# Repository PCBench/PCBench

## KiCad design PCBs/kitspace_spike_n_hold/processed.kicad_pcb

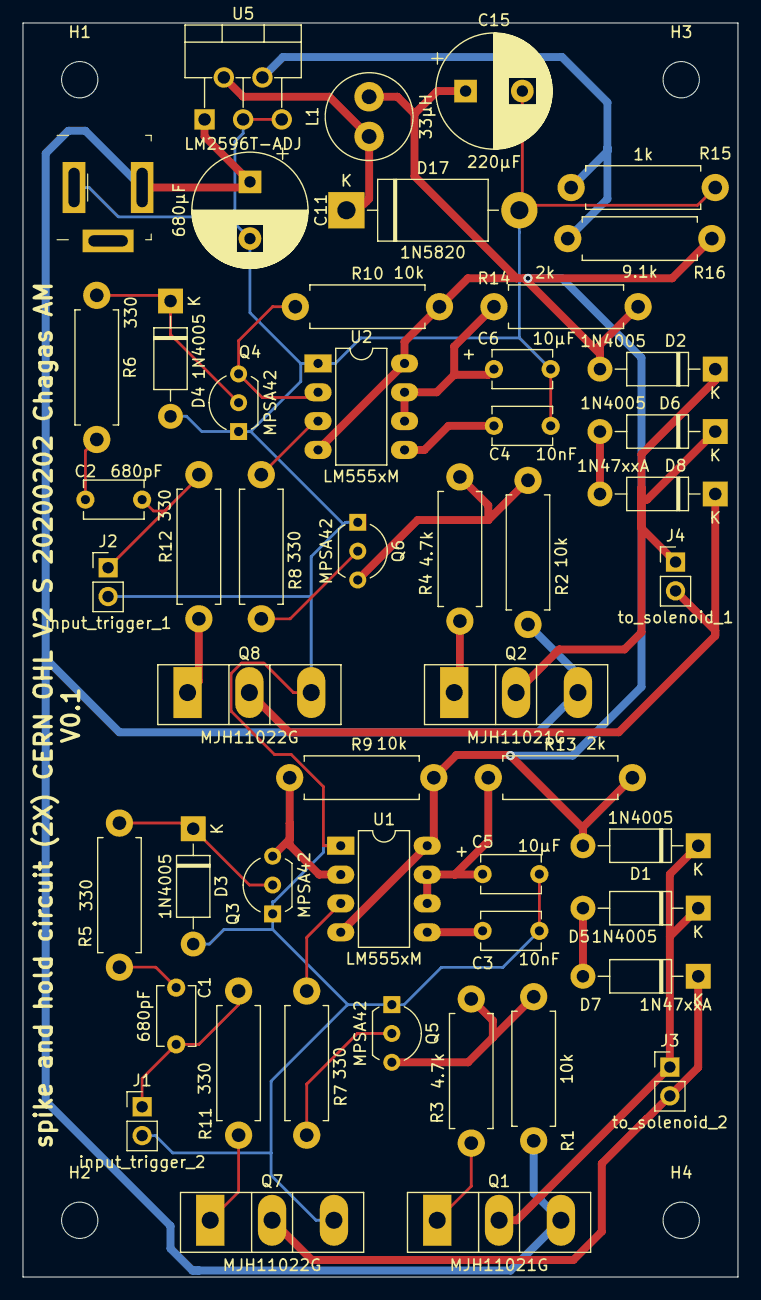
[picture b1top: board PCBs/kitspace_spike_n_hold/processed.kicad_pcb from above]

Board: 2 copper layers, 63.0 x 110.5 mm, 54 parts (0 on the bottom side), 33 nets.

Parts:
C1, C2: 680pF; C_Disc_D5.1mm_W3.2mm_P5.00mm
C3, C4: 10nF; C_Disc_D5.1mm_W3.2mm_P5.00mm
C5, C6: 10µF; C_Disc_D5.1mm_W3.2mm_P5.00mm
C11: 680µF; CP_Radial_D10.0mm_P5.00mm
C15: 220µF; CP_Radial_D10.0mm_P5.00mm
D1, D2, D3, D4, D5, D6: 1N4005; D_DO-41_SOD81_P10.16mm_Horizontal
D7, D8: 1N47xxA; D_DO-41_SOD81_P10.16mm_Horizontal
D17: 1N5820; D_DO-201AD_P15.24mm_Horizontal
H1, H2, H3, H4: MountingHole; MountingHole_3.2mm_M3
J1: input_trigger_2; PinHeader_1x02_P2.54mm_Vertical
J2: input_trigger_1; PinHeader_1x02_P2.54mm_Vertical
J3: to_solenoid_2; PinHeader_1x02_P2.54mm_Vertical
J4: to_solenoid_1; PinHeader_1x02_P2.54mm_Vertical
J9: Barrel_Jack_MountingPin; Barrel_Jack_5.5mmODx2.1mmID_PJ-202A
L1: 33µH; L_Radial_D7.5mm_P3.50mm_Fastron_07P
Q1, Q2: MJH11021G; TO-247-3_Vertical
Q3, Q4, Q5, Q6: MPSA42; TO-92L_Inline_Wide
Q7, Q8: MJH11022G; TO-247-3_Vertical
R1, R2, R9, R10: 10k; R_Axial_DIN0411_L9.9mm_D3.6mm_P12.70mm_Horizontal
R3, R4: 4.7k; R_Axial_DIN0411_L9.9mm_D3.6mm_P12.70mm_Horizontal
R5, R6, R7, R8, R11, R12: 330; R_Axial_DIN0411_L9.9mm_D3.6mm_P12.70mm_Horizontal
R13, R14: 2k; R_Axial_DIN0411_L9.9mm_D3.6mm_P12.70mm_Horizontal
R15: 1k; R_Axial_DIN0411_L9.9mm_D3.6mm_P12.70mm_Horizontal
R16: 9.1k; R_Axial_DIN0411_L9.9mm_D3.6mm_P12.70mm_Horizontal
U1, U2: LM555xM; DIP-8_W7.62mm_LongPads
U5: LM2596T-ADJ; TO-220-5_P3.4x3.7mm_StaggerOdd_Lead3.8mm_Vertical

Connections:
+12V: C15.1, D1.2, D2.2, L1.2, R9.2, R10.2, R13.2, R14.2, R16.2, U1.4, U1.8, U2.4, U2.8
+24V: C11.1, J9.1, Q1.3, Q2.3, R1.1, R2.1, U5.1
GND: C3.1, C4.1, C5.2, C6.2, C11.2, C15.2, D3.2, D4.2, D17.2, J1.2, J2.2, J9.2, Q3.1, Q4.1, Q5.1, Q6.1, Q7.3, Q8.3, R15.1, U1.1, U2.1, U5.3, U5.5
unnamed: C1.1, R5.2
unnamed: C2.1, R6.2
unnamed: C3.2, U1.5
unnamed: C4.2, U2.5
unnamed: C5.1, R13.1, U1.6, U1.7
unnamed: C6.1, R14.1, U2.6, U2.7
unnamed: D1.1, D5.1, J3.1, Q1.2
unnamed: D2.1, D6.1, J4.1, Q2.2
unnamed: D3.1, Q3.2, R5.1
unnamed: D4.1, Q4.2, R6.1
unnamed: D5.2, D7.2
unnamed: D6.2, D8.2
unnamed: D7.1, J3.2, Q7.2
unnamed: D8.1, J4.2, Q8.2
unnamed: D17.1, L1.1, U5.2
unnamed: Q1.1, R3.2
unnamed: Q2.1, R4.2
unnamed: Q3.3, R9.1, U1.2
unnamed: Q4.3, R10.1, U2.2
unnamed: Q5.2, R7.1
unnamed: Q5.3, R1.2, R3.1
unnamed: Q6.2, R8.1
unnamed: Q6.3, R2.2, R4.1
unnamed: Q7.1, R11.1
unnamed: Q8.1, R12.1
unnamed: R15.2, R16.1, U5.4
input_trigger1: C2.2, J2.1, R12.2
input_trigger2: C1.2, J1.1, R11.2
timed_trigger1: R8.2, U2.3
timed_trigger2: R7.2, U1.3

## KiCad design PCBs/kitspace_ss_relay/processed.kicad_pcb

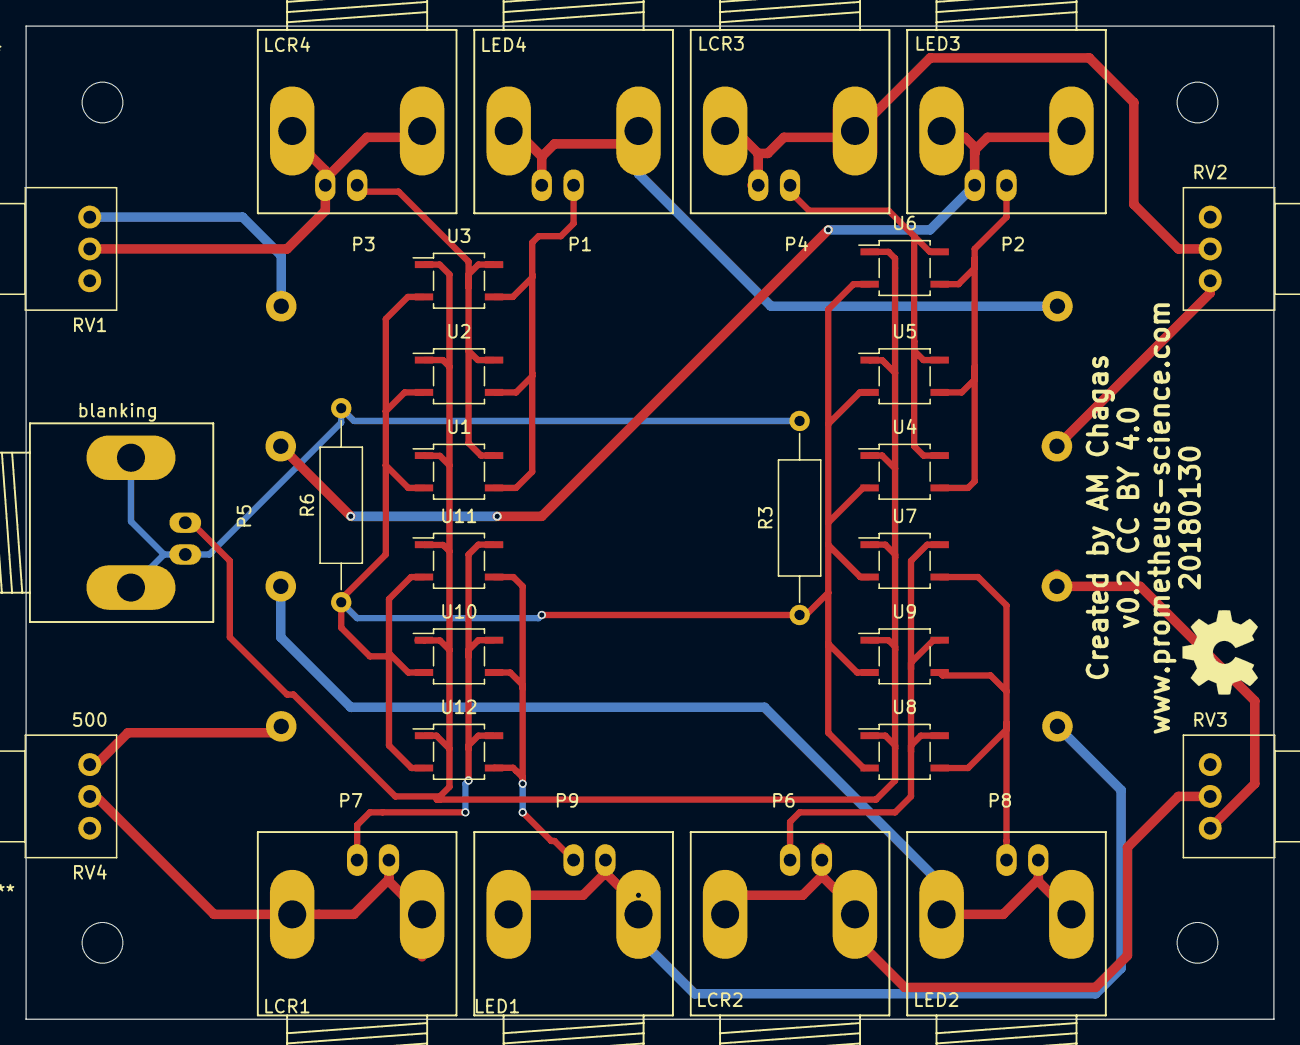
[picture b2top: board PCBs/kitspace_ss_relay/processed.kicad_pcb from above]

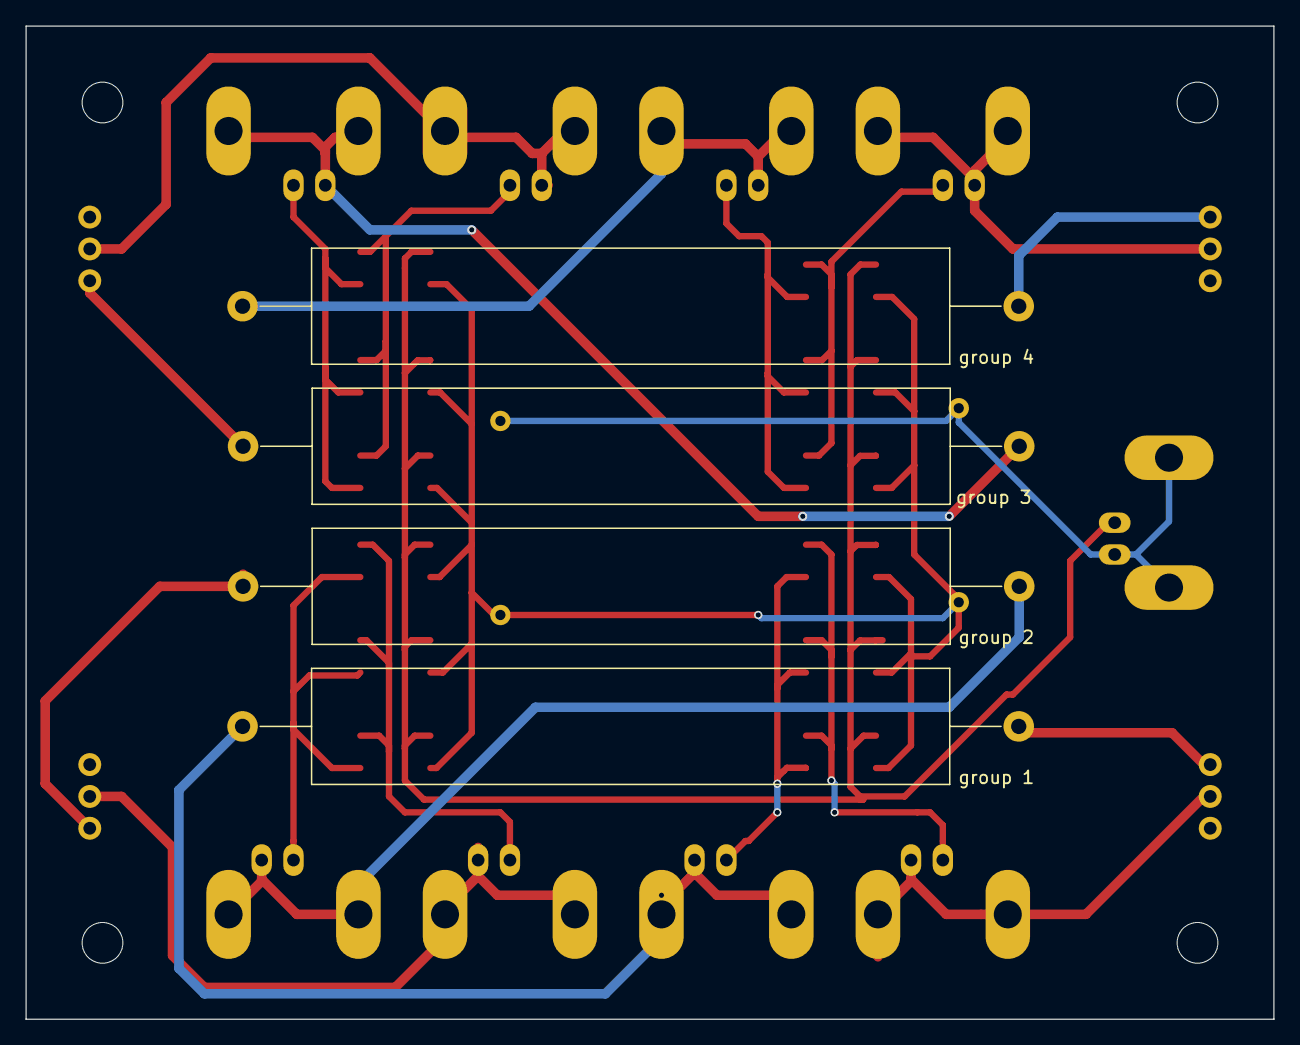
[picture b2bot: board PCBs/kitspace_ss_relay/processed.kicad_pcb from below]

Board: 2 copper layers, 98.0 x 78.0 mm, 31 parts (4 on the bottom side), 23 nets.

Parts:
P1: LED4; BNC_Socket_TYCO-AMP_LargePads
P2: LED3; BNC_Socket_TYCO-AMP_LargePads
P3: LCR4; BNC_Socket_TYCO-AMP_LargePads
P4: LCR3; BNC_Socket_TYCO-AMP_LargePads
P5: blanking; BNC_Socket_TYCO-AMP_LargePads
P6: LCR2; BNC_Socket_TYCO-AMP_LargePads
P7: LCR1; BNC_Socket_TYCO-AMP_LargePads
P8: LED2; BNC_Socket_TYCO-AMP_LargePads
P9: LED1; BNC_Socket_TYCO-AMP_LargePads
R3, R6: 270; R_Axial_DIN0309_L9.0mm_D3.2mm_P15.24mm_Horizontal
RV1, RV2, RV3, RV4: 500; Potentiometer_Alps_RK097_Single_Vertical
U1, U2, U3, U4, U5, U6, U7, U8, U9, U10, U11, U12: TLP291; SOP-4_3.8x4.1mm_Pitch2.54mm
group 1, group 2, group 3, group 4: 10; R_Axial_Power_L50.0mm_W9.0mm_P60.96mm

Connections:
GND: P5.2, R3.2, R6.2
unnamed: P1.1, U1.3, U2.3, U3.3
unnamed: P1.2, group 4.1
unnamed: P2.1, U4.3, U5.3, U6.3
unnamed: P2.2, group 3.1
unnamed: P3.1, U1.4, U2.4, U3.4
unnamed: P3.2, RV1.2
unnamed: P4.1, U4.4, U5.4, U6.4
unnamed: P4.2, RV2.2
unnamed: P5.1, U1.1, U2.1, U3.1, U4.1, U5.1, U6.1, U7.1, U8.1, U9.1, U10.1, U11.1, U12.1
unnamed: P6.1, U7.4, U8.4, U9.4
unnamed: P6.2, RV3.2
unnamed: P7.1, U10.4, U11.4, U12.4
unnamed: P7.2, RV4.2
unnamed: P8.1, U7.3, U8.3, U9.3
unnamed: P8.2, group 2.1
unnamed: P9.1, U10.3, U11.3, U12.3
unnamed: P9.2, group 1.1
unnamed: RV1.1, group 4.2
unnamed: RV2.1, group 3.2
unnamed: R3.1, R6.1, U1.2, U2.2, U3.2, U4.2, U5.2, U6.2, U7.2, U8.2, U9.2, U10.2, U11.2, U12.2
unnamed: RV3.1, group 2.2
unnamed: RV4.1, group 1.2

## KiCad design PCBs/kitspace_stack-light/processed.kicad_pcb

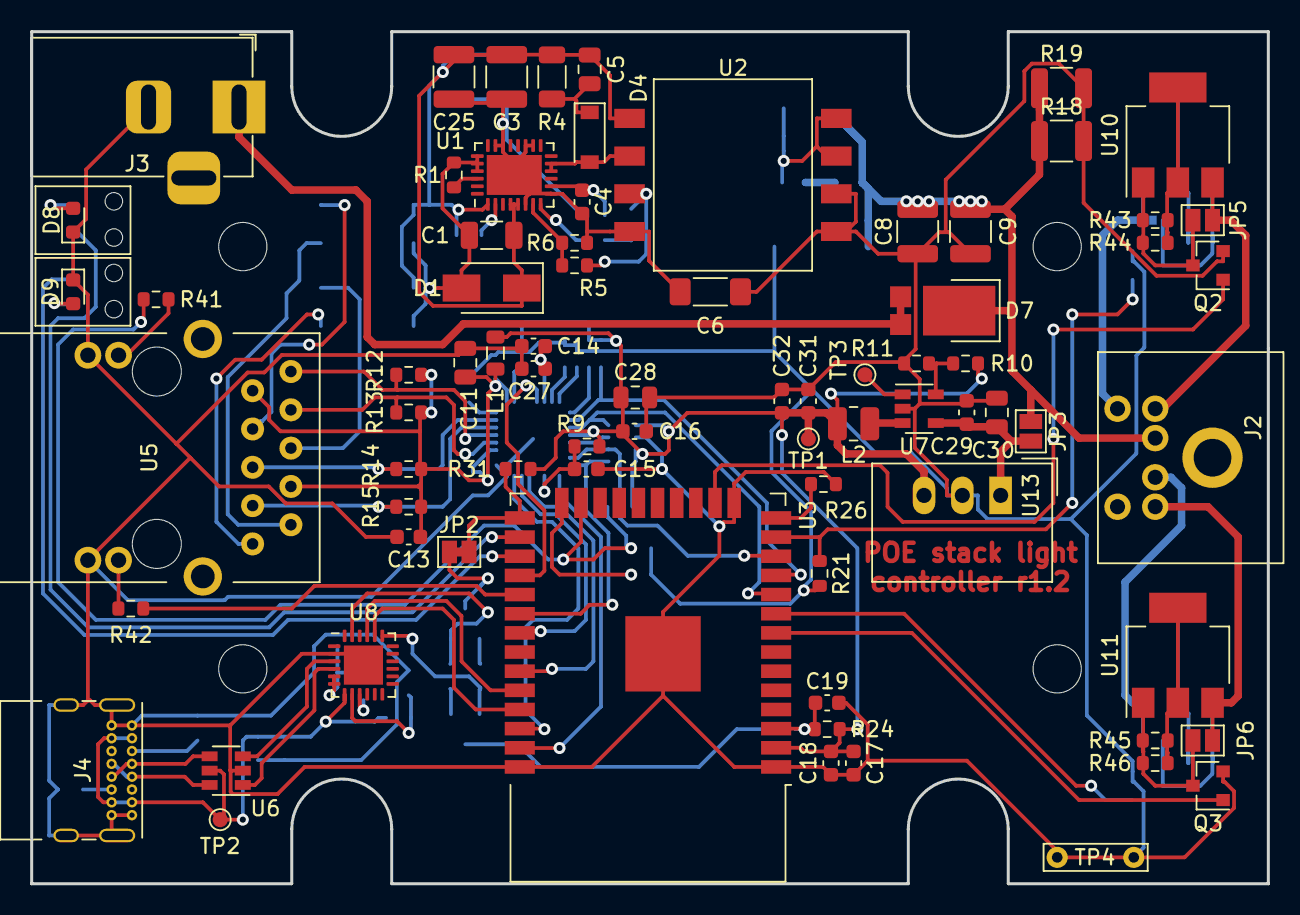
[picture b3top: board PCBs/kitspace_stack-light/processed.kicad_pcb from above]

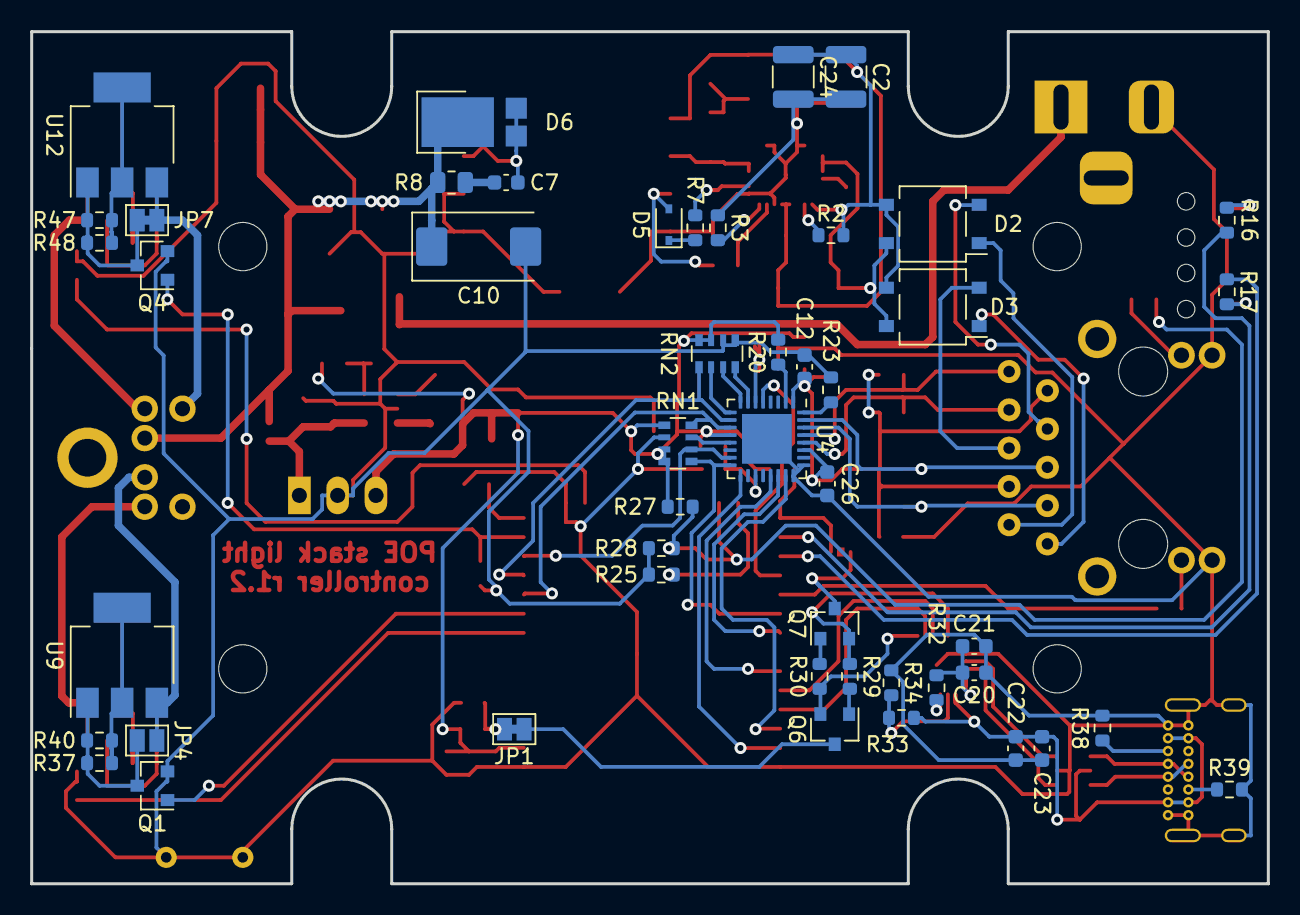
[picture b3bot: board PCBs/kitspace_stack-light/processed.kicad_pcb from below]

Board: 2 copper layers, 82.0 x 56.5 mm, 129 parts (48 on the bottom side), 94 nets.

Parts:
C1: 100n; C_1206_3216Metric
C2, C3, C24, C25: 2u2; C_1210_3225Metric
C4: 1U; C_0603_1608Metric
C5: 10n; C_0805_2012Metric
C6: 1000p; C_1806_4516Metric
C7: 1n; C_0603_1608Metric
C8, C9: 22u; C_1210_3225Metric
C10: 220u; CP_EIA-7343-31_Kemet-D
C11, C28: 22u; C_0805_2012Metric
C12, C14, C16, C18, C21, C23, C26, C29: 100n; C_0603_1608Metric
C13: 100nf; C_0603_1608Metric
C15, C19: 1u; C_0603_1608Metric
C17, C31, C32: 10u; C_0603_1608Metric
C20, C22: 4u7; C_0603_1608Metric
C27: 2u2; C_0603_1608Metric
C30: 10u; C_0805_2012Metric
D1: SMAJ58A; D_SMA
D2, D3: MB4S; TO-269AA
D4: BAV21; D_SOD-123
D5: 1N4148; D_SOD-323
D6, D7: SBR8U60P5; D_PowerDI-5
D8, D9: LED; LED_0603_1608Metric
H1, H2, H3, H4: MountingHole; MountingHole_3.2mm_M3
H5, H6: MountingHole; SLP3-150-150-R
J2: Mini-DIN-6; MD60S
J3: Barrel_Jack_Switch; BarrelJack_Horizontal
J4: USB_C_Receptacle_USB2.0; USB_C_Receptacle_GCT_USB4085
JP1, JP2, JP7: Jumper; SolderJumper-2_P1.3mm_Bridged_Pad1.0x1.5mm
JP3, JP4, JP5, JP6: Jumper; SolderJumper-2_P1.3mm_Open_Pad1.0x1.5mm
L1: FB; L_0805_2012Metric
L2: 10u; L_1008_2520Metric
Q1, Q2, Q3, Q4: 2N7002; SOT-23
Q6, Q7: BC817-40; SOT-23
R1: 62; R_0603_1608Metric
R2: 24K9; R_0603_1608Metric
R3: 52K3; R_0603_1608Metric
R4: 10K; R_1206_3216Metric
R5: 105k; R_0603_1608Metric
R6, R11: 20k; R_0603_1608Metric
R7, R38, R39: 5K1; R_0603_1608Metric
R8: 20; R_0805_2012Metric
R9, R20, R21, R24, R25, R26, R27, R31: 10k; R_0603_1608Metric
R10: 61k9; R_0603_1608Metric
R12, R13, R14, R15: 49.9; R_0603_1608Metric
R16, R17, R41, R42: 330; R_0603_1608Metric
R18: 330; R_1210_3225Metric
R19: DNP; R_1210_3225Metric
R23: 12.1k; R_0603_1608Metric
R28, R47, R48: DNP; R_0603_1608Metric
R29, R30: 220; R_0603_1608Metric
R32: 1k; R_0603_1608Metric
R33: 22k1; R_0603_1608Metric
R34: 47k5; R_0603_1608Metric
R37, R40, R43, R44, R45, R46: 33; R_0603_1608Metric
RN1, RN2: 2k2; R_Array_Convex_4x0603
TP1, TP2, TP3: TestPoint; TestPoint_Pad_D1.0mm
TP4: TestPoint; TestPoint_Bridge_Pitch5.08mm_Drill0.7mm
U1: MP8007; QFN-28-1EP_4x5mm_P0.5mm_EP2.65x3.65mm
U2: POE70P-12L; Transformer_Coilcraft_POE70P
U3: ESP32-WROOM-32D; ESP32-WROOM-32
U4: LAN8710A-EZC; QFN-32-1EP_5x5mm_P0.5mm_EP3.3x3.3mm
U5: ARJM11C7-114-BA
U6: USBLC6-2SC6; SOT-23-6
U7: TPS560200; SOT-23-5
U8: CP2102N-A01-GQFN24; QFN-24-1EP_4x4mm_P0.5mm_EP2.6x2.6mm
U9, U10, U11: AMS1117; SOT-223-3_TabPin2
U12: AMS1117-DNP; SOT-223-3_TabPin2
U13: TSR_1-2433; Converter_DCDC_TRACO_TSR-1_THT

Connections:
+3V3: C16.1, C17.1, C18.1, C28.1, C31.1, C32.1, L1.1, L2.2, R9.1, R10.1, R20.2, R24.2, R27.2, R31.1, RN1.1, RN1.3, RN1.4, RN2.3, RN2.4, TP1.1, U3.2, U4.12, U13.3
+12V: C8.1, C9.1, C10.1, D6.1, D7.1, J2.1, JP3.1, R8.2, R18.1, R19.1
/Ethernet Controller/RDN: R15.1, U4.30, U5.3
/Ethernet Controller/RDP: R14.1, U4.31, U5.5
/Ethernet Controller/TDN: R13.1, U4.28, U5.8
/Ethernet Controller/TDP: R12.1, U4.29, U5.10
/Output/Drive_Buzzer: J2.5, JP7.1, U12.3
/Output/Drive_Green: J2.4, JP6.1, U11.3
/Output/Drive_Red: J2.2, JP4.1, U9.3
/Output/Drive_Yellow: J2.3, JP5.1, U10.3
/Processor/BOOT_SEL: JP2.2, R31.2, U3.25
/Processor/RESET: C19.1, JP1.2, R24.1, U3.3
/Processor/UART_RX: U3.34, U8.21
/Processor/UART_TX: U3.35, U8.20
/Processor/USB_D+: U6.3, U8.3
/Processor/USB_D-: U6.1, U8.4
/Processor/USB_VBUS: C22.2, C23.2, J4.A4, J4.A9, J4.B4, J4.B9, R33.2, TP2.1, U6.5, U8.7
Buzzer: Q4.1, R21.1, U3.13
ETH_CLKIN: U3.28, U4.5
ETH_CRS_DV: RN1.6, U3.12, U4.15
ETH_MDC: U3.37, U4.17
ETH_MDIO: RN1.5, U3.30, U4.16
ETH_RXD0: RN1.8, U3.10, U4.11
ETH_RXD1: RN2.5, U3.11, U4.10
ETH_TXD0: U3.31, U4.22
ETH_TXD1: U3.36, U4.23
ETH_TX_EN: U3.33, U4.21
GND: C6.2, C8.2, C9.2, C10.2, C11.1, C12.1, C13.1, C14.2, C15.2, C16.2, C17.2, C18.2, C19.2, C20.1, C21.1, C22.1, C23.1, C26.1, C27.2, C28.2, C29.2, C30.2, C31.2, C32.2, D8.1, D9.1, J3.2, J4.A1, J4.A12, J4.B1, J4.B12, J4.S1, Q1.2, Q2.2, Q3.2, Q4.2, R11.2, R18.2, R19.2, R21.2, R23.2, R25.2, R26.2, R28.2, R34.1, R38.1, R39.2, RN1.2, RN2.1, RN2.2, TP4.1, U2.7, U2.8, U3.1, U3.15, U3.38, U3.39, U4.24, U4.25, U4.33, U5.12, U5.14, U6.2, U7.2, U8.2, U8.25, U13.2
GNDPWR: C2.2, C3.2, C4.2, C6.1, C24.2, C25.2, R3.1, R6.1, U1.6, U1.9, U1.16, U1.17, U1.20, U1.21, U1.29, U2.1
Green: Q3.1, U3.8
LED_ARTNET: R17.1, U3.27
LED_LOCATE: R16.1, U3.26
LED_net: R42.2, U3.29
LED_status: R27.1, R28.1, R41.2, U3.23
unnamed: C4.1, R7.1, U1.10
unnamed: C5.2, D4.1, R4.1
unnamed: C7.1, D6.2, U2.5, U2.6
unnamed: C7.2, R8.1
unnamed: C11.2, C12.2, C13.2, C26.2, L1.2, R12.2, R13.2, R14.2, R15.2, U4.1, U4.27, U5.4, U5.9
unnamed: C14.1, C27.1, U4.6
unnamed: C15.1, R9.2, U4.19
unnamed: C20.2, C21.2, R32.1, U8.5, U8.6
unnamed: C29.1, C30.1, JP3.2, U7.4, U13.1
unnamed: D4.2, U1.12, U1.13, U2.3
unnamed: D5.1, R7.2
unnamed: D5.2, R5.2, U2.2
unnamed: D7.2, J3.1
unnamed: D8.2, R16.2
unnamed: D9.2, R17.2
unnamed: J4.A5, R38.2
unnamed: J4.A6, J4.B6, U6.4
unnamed: J4.A7, J4.B7, U6.6
unnamed: J4.B5, R39.1
unnamed: JP1.1, Q6.3
unnamed: JP2.1, Q7.3
unnamed: JP4.2, Q1.3, R37.1, R40.1, U9.1
unnamed: JP5.2, Q2.3, R43.1, R44.1, U10.1
unnamed: JP6.2, Q3.3, R45.1, R46.1, U11.1
unnamed: JP7.2, Q4.3, R47.1, R48.1, U12.1
unnamed: L2.1, U7.3
unnamed: Q6.1, R29.2
unnamed: Q6.2, R30.1, U8.19
unnamed: Q7.1, R30.2
unnamed: Q7.2, R29.1, U8.23
unnamed: R1.2, U1.26
unnamed: R2.1, U1.2
unnamed: R3.2, U1.8
unnamed: R5.1, R6.2, U1.7
unnamed: R10.2, R11.1, U7.5
unnamed: R20.1, U4.2
unnamed: R23.1, U4.32
unnamed: R25.1, U3.24
unnamed: R26.1, U3.14
unnamed: R32.2, U8.9
unnamed: R33.1, R34.2, U8.8
unnamed: R37.2, R40.2, U9.2
unnamed: R41.1, U5.11
unnamed: R42.1, U5.13
unnamed: R43.2, R44.2, U10.2
unnamed: R45.2, R46.2, U11.2
unnamed: R47.2, R48.2, U12.2
unnamed: RN1.7, U4.13
unnamed: RN2.6, U4.9
unnamed: RN2.7, U4.8
unnamed: RN2.8, U4.7
unnamed: TP3.1, U7.1
POE_V1+: D2.2, U5.7
POE_V1-: D2.1, U5.2
POE_V2+: D3.2, U5.6
POE_V2-: D3.1, U5.1
POE_VIN: C1.1, C2.1, C3.1, C5.1, C24.1, C25.1, D1.1, D2.3, D3.3, R2.2, R4.2, U1.1, U1.4, U1.5, U2.4
POE_VSS: C1.2, D1.2, D2.4, D3.4, R1.1, U1.23, U1.24, U1.25
Red: Q1.1, U3.9
Yellow: Q2.1, U3.16

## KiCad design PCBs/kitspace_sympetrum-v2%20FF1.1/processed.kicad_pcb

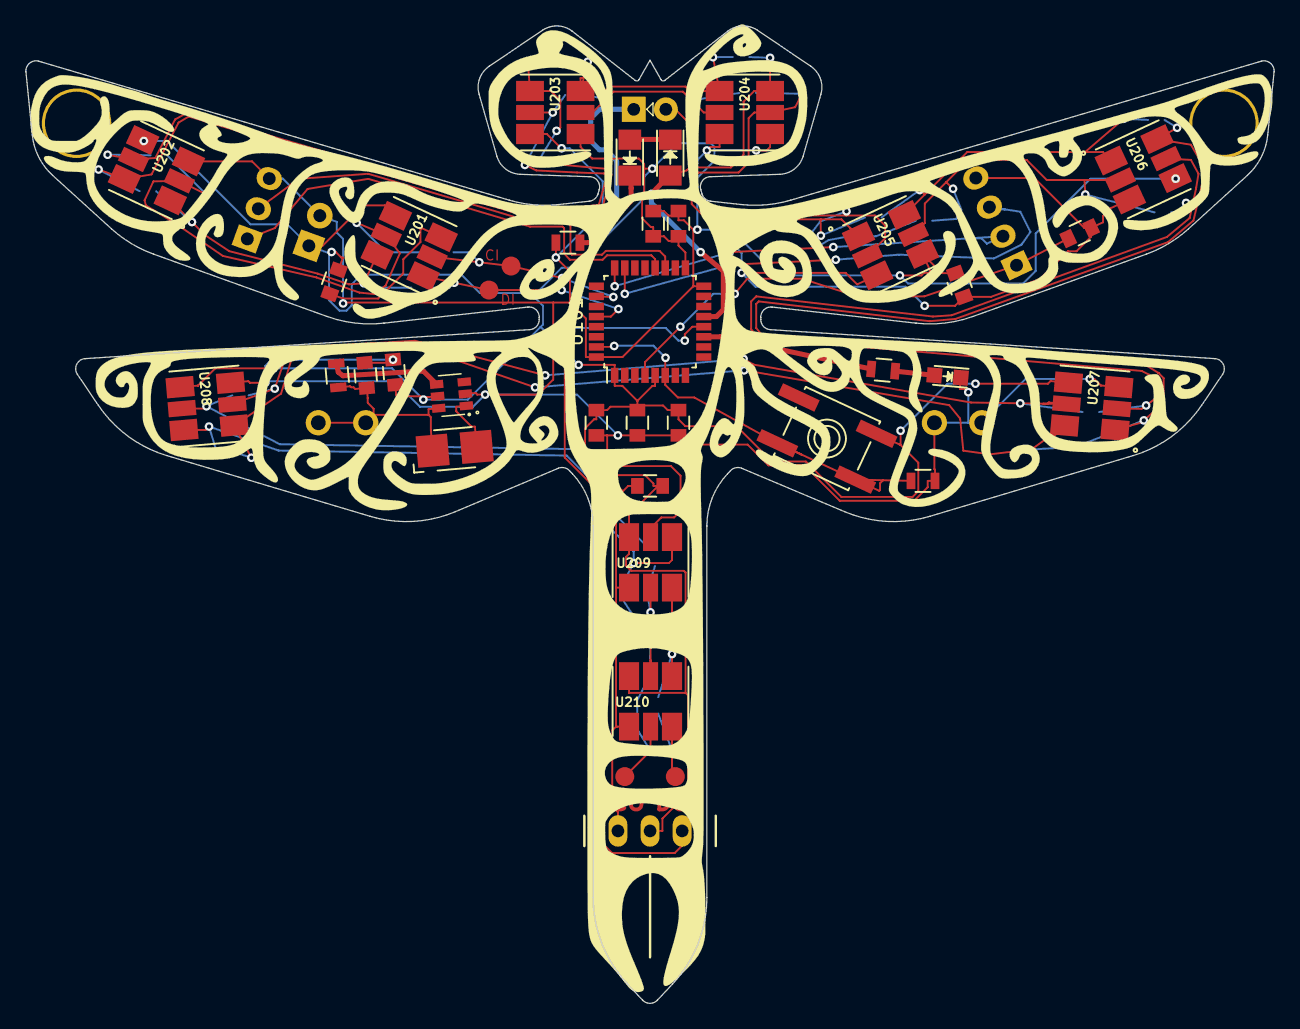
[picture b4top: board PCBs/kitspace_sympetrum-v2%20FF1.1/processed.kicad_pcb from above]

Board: 2 copper layers, 98.8 x 77.3 mm, 64 parts (0 on the bottom side), 39 nets.

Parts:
B301: BCAAAPC_+_BCAAPC; BCAAAPC+BCAAPC-ChinaFixed
C101, C104, C105: 0.1uF; C_0805
C102: 10nF; C_0805
C103: 1uF; C_0805
C106, C301, C302: 4.7uF; C_0805
C201, C202, C203: 22uF; C_0805
D101: USER_LED; LED_0805
D102, D103: IR25-21C/TR8; LED_1206
D104: PTH_LED; LED-5MM-NoSilk
H101, H102: Hole_5mm; Home_5mm
JP201, JP202, JP203, JP204, JP205, JP206, JP207, JP208, JP209, JP210, JP211, JP212, JP213, JP214, JP215, JP216, JP217, JP218, JP219, JP220: Jumper_NO_Small; SOLDER-JUMPER_1-WAY
J_PROG101: CONN_01x04; Pin_Header_Straight_1x04
J_PWR301: CONN_01x02; Pin_Header_Straight_1x02
J_UART101: CONN_01x03; Pin_Header_Straight_1x03
L301: 4.7uH; Inductor_1212
R101: 10k; R_0805
R102: 0R; R_0805
R103: 36R; R_0805
R301: 1M; R_0805
SW101: DFU; SW_SPST_EVQP0_DPLIT
TP_LED_CLK101: TEST_1P; Measurement_Point_Round-SMD-Pad_Small
TP_LED_CLK_O101: TEST_1P; Measurement_Point_Round-SMD-Pad_Small
TP_LED_MOSI101: TEST_1P; Measurement_Point_Round-SMD-Pad_Small
TP_LED_MOSI_O101: TEST_1P; Measurement_Point_Round-SMD-Pad_Small
U101: STM32F030K6T6; LQFP-32_7x7mm_Pitch0.8mm
U102: TSSP58P38; TO-220_Neutral123_Vertical_LayDown-NoSilk
U201, U202, U203, U204, U205, U206, U207, U208, U209, U210: APA102_5050; LED-5050
U301: AAT1217-3.3; SOT-23-6

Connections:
+3V3: C102.1, C103.1, C104.1, C105.1, C106.1, C201.1, C202.1, C203.1, C302.1, J_PWR301.1, SW101.3, U101.1, U101.5, U101.17, U102.3, U201.4, U202.4, U203.4, U204.4, U205.4, U206.4, U207.4, U208.4, U209.4, U210.4, U301.5
+BATT: B301.1, C301.1, L301.1, R301.1, U301.6
/IR_RX: U101.12, U102.1
/IR_TX: D102.2, D104.2, U101.13
/LEDArray/MOSI-OUT: JP218.2, TP_LED_MOSI_O101.1, U210.6
/LEDArray/SCK-OUT: JP217.2, TP_LED_CLK_O101.1, U210.5
/LED_CLK: JP201.1, TP_LED_CLK101.1, U101.26, U201.2
/LED_MOSI: JP202.1, TP_LED_MOSI101.1, U101.28, U201.1
/SWDCLK: J_PROG101.2, U101.24
/SWDIO: J_PROG101.3, U101.23
/USART1_RX: J_UART101.1, U101.20
/USART1_TX: J_UART101.2, U101.19
/USER_BUTTON: R101.1, SW101.2, SW101.4, U101.6, U101.31
/USER_LED: R102.2, U101.11
/nRST: C101.1, J_PROG101.1, U101.4
GND: B301.2, C101.2, C102.2, C103.2, C104.2, C105.2, C106.2, C201.2, C202.2, C203.2, C301.2, C302.2, D101.1, J_PROG101.4, J_PWR301.2, J_UART101.3, R101.2, R103.1, U101.16, U101.32, U102.2, U201.3, U202.3, U203.3, U204.3, U205.3, U206.3, U207.3, U208.3, U209.3, U210.3, U301.2
unnamed: D101.2, R102.1
unnamed: D102.1, D103.2
unnamed: D103.1, D104.1, R103.2
unnamed: JP201.2, JP207.1, U201.5, U202.2
unnamed: JP202.2, JP208.1, U201.6, U202.1
unnamed: JP203.1, JP219.2, U205.5, U206.2
unnamed: JP203.2, JP205.1, U206.5, U207.2
unnamed: JP204.1, JP220.2, U205.6, U206.1
unnamed: JP204.2, JP206.1, U206.6, U207.1
unnamed: JP205.2, JP209.1, U207.5, U208.2
unnamed: JP206.2, JP210.1, U207.6, U208.1
unnamed: JP207.2, JP211.1, U202.5, U203.2
unnamed: JP208.2, JP212.1, U202.6, U203.1
unnamed: JP209.2, JP213.1, U208.5, U209.2
unnamed: JP210.2, JP214.1, U208.6, U209.1
unnamed: JP211.2, JP215.1, U203.5, U204.2
unnamed: JP212.2, JP216.1, U203.6, U204.1
unnamed: JP213.2, JP217.1, U209.5, U210.2
unnamed: JP214.2, JP218.1, U209.6, U210.1
unnamed: JP215.2, JP219.1, U204.5, U205.2
unnamed: JP216.2, JP220.1, U204.6, U205.1
unnamed: L301.2, U301.1
unnamed: R301.2, U301.4

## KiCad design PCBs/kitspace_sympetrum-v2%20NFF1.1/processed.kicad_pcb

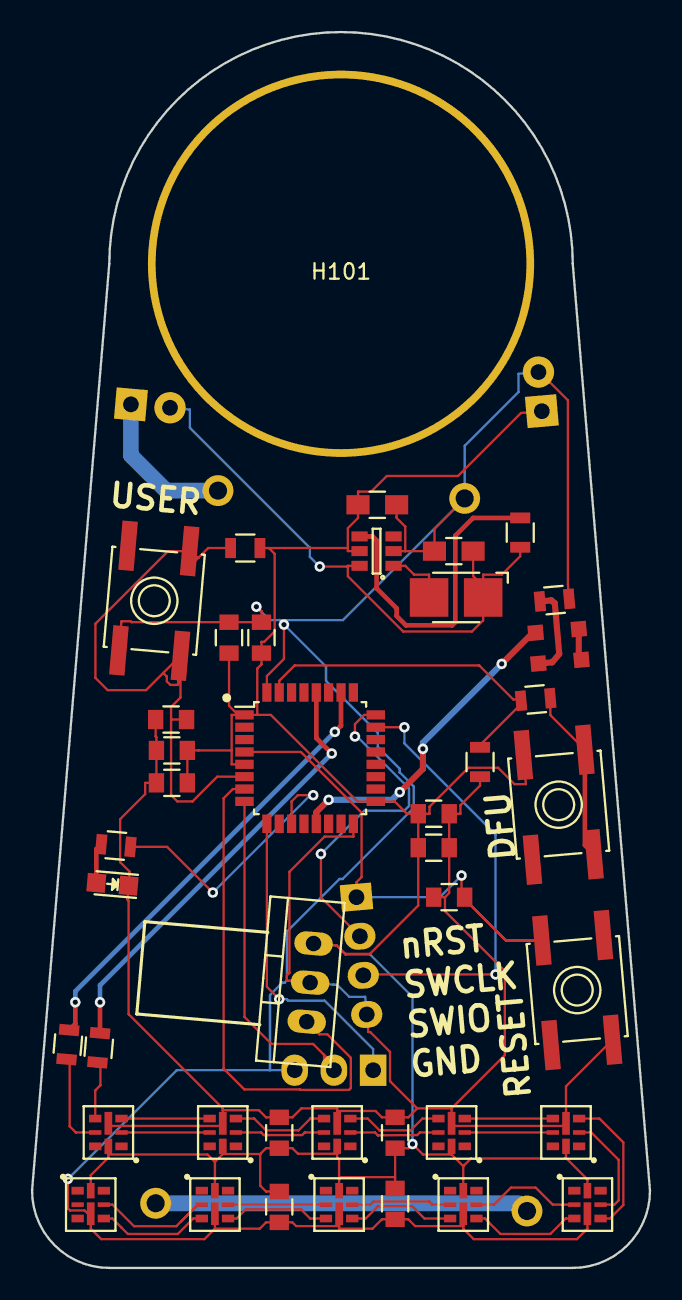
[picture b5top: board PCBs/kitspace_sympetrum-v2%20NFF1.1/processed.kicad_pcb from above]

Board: 2 copper layers, 40.0 x 80.0 mm, 49 parts (0 on the bottom side), 43 nets.

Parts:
B301, B302: BCAAAPC
C101, C102: 0.1µF; C_0805
C103: 10nF; C_0805
C104, C106: 10µF; C_0805
C105: 1µF; C_0805
C107, C108: 100nF; C_0805
C201, C202, C203, C204: 22µF; C_0805
C301, C302: 4.7uF; C_0805_HandSoldering
D101: USER_LED; LED_0805
D102, D103: IR12-21C/TR8; Everlight-IR12-21C-TR8
H101: Hole_-_24mm; Hole-24mm
JP301: JP_POWER; Socket_Strip_Straight_1x02
L301: 4.7uH; Inductor_1212
P101: PROG_HEADER; Pin_Header_Straight_1x04
P102: USART2; Pin_Header_Straight_1x03
P301: DBG_PWR; Pin_Header_Straight_1x02
R1, R102: 10kΩ; R_0805
R101: 1kΩ; R_0805
R103, R104, R105: 0Ω; R_0805
R106: 36Ω; R_0805
R301: 1MΩ; R_0805
SW1: RESET; SW_SPST_EVQP0_DPLIT
SW2: DFU; SW_SPST_EVQP0_DPLIT
SW103: USER; SW_SPST_EVQP0_DPLIT
U101: STM32F051K8T6; LQFP-32_7x7mm_Pitch0.8mm
U102: TSSP58P38; TO-220_Neutral123_Vertical_LayDown
U201, U202, U203, U204, U205, U206, U207, U208, U209, U210: APA102_2020; APA102_2020_LED_Complex_Split
U301: AAT1217-3.3; SOT-23-6

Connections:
+3V3: C103.1, C104.1, C105.1, C106.1, C107.1, C108.1, C201.1, C202.1, C203.1, C204.1, C302.1, P301.1, R102.2, SW2.3, U101.1, U101.5, U101.17, U102.3, U201.7, U202.7, U203.7, U204.7, U205.7, U206.7, U207.7, U208.7, U209.7, U210.7, U301.5
+BATT: B302.1, JP301.1
/IR_RX: U101.7, U102.1
/IR_TX: D102.2, U101.13
/LEDArray/MOSI-IN: R104.1, U201.4
/LEDArray/SCK-IN: R105.1, U201.5
/LED_CLK: R105.2, U101.26
/LED_MOSI: R104.2, U101.28
/Power/VIN: C301.1, JP301.2, L301.1, R301.1, U301.6
/SWDCLK: P101.2, U101.24
/SWDIO: P101.3, U101.23
/USART2_RX: P102.1, U101.9
/USART2_TX: P102.2, U101.8
/USER_BUTTON: C102.1, R102.1, SW103.1, SW103.3, U101.6
/USER_LED: R103.2, U101.11
/nRST: C101.1, P101.1, SW1.2, U101.4
GND: B301.2, C101.2, C102.2, C103.2, C104.2, C105.2, C106.2, C107.2, C108.2, C201.2, C202.2, C203.2, C204.2, C301.2, C302.2, D101.1, P101.4, P102.3, P301.2, R101.2, R106.1, SW1.3, SW103.4, U101.16, U101.32, U102.2, U201.8, U202.8, U203.8, U204.8, U205.8, U206.8, U207.8, U208.8, U209.8, U210.8, U301.2
unnamed: B301.1, B302.2
unnamed: D101.2, R103.1
unnamed: D102.1, D103.2
unnamed: D103.1, R106.2
unnamed: L301.2, U301.1
unnamed: R1.1, SW2.2, SW2.4
unnamed: R1.2, R101.1, U101.31
unnamed: R301.2, U301.4
unnamed: U201.2, U203.5
unnamed: U201.3, U203.4
unnamed: U202.2, U204.5
unnamed: U202.3, U204.4
unnamed: U202.4, U209.3
unnamed: U202.5, U209.2
unnamed: U203.2, U205.5
unnamed: U203.3, U205.4
unnamed: U204.2, U206.5
unnamed: U204.3, U206.4
unnamed: U205.2, U207.5
unnamed: U205.3, U207.4
unnamed: U206.2, U208.5
unnamed: U206.3, U208.4
unnamed: U207.2, U209.5
unnamed: U207.3, U209.4
unnamed: U208.2, U210.5
unnamed: U208.3, U210.4

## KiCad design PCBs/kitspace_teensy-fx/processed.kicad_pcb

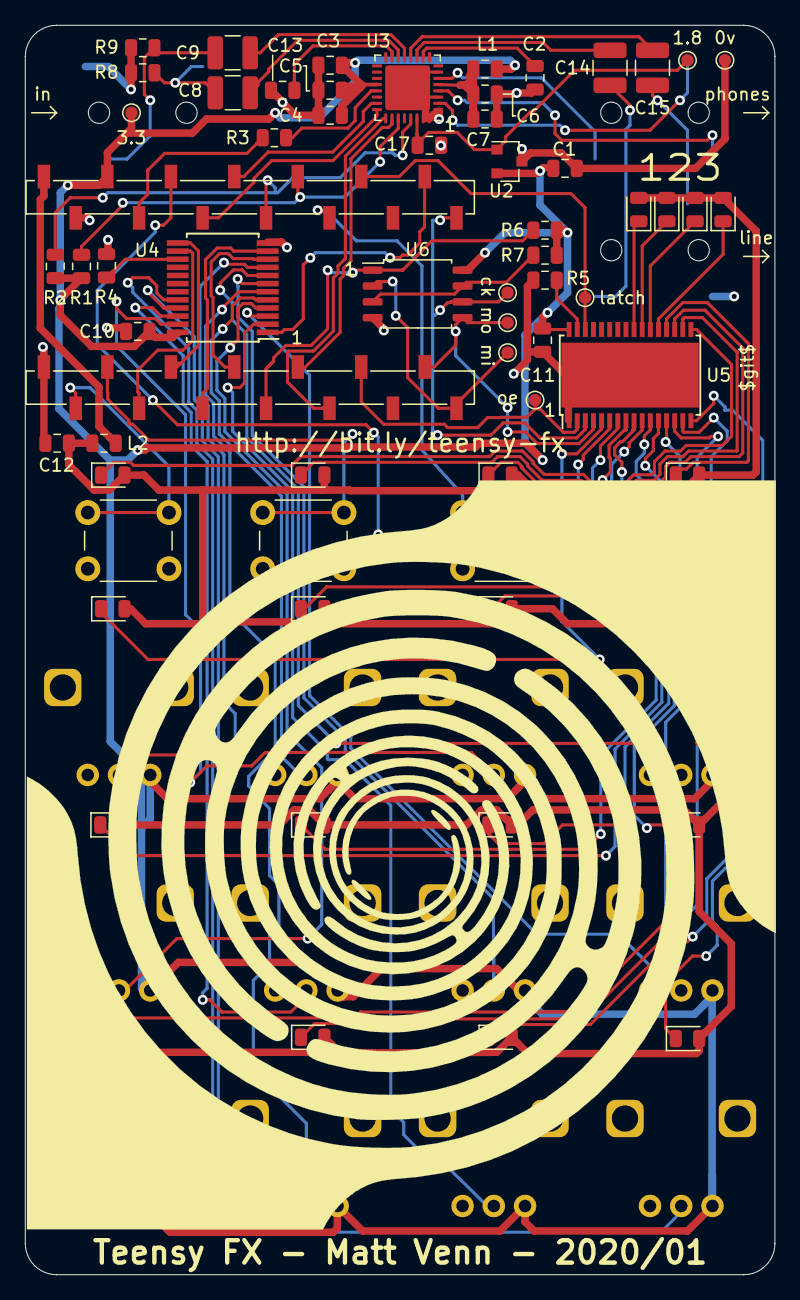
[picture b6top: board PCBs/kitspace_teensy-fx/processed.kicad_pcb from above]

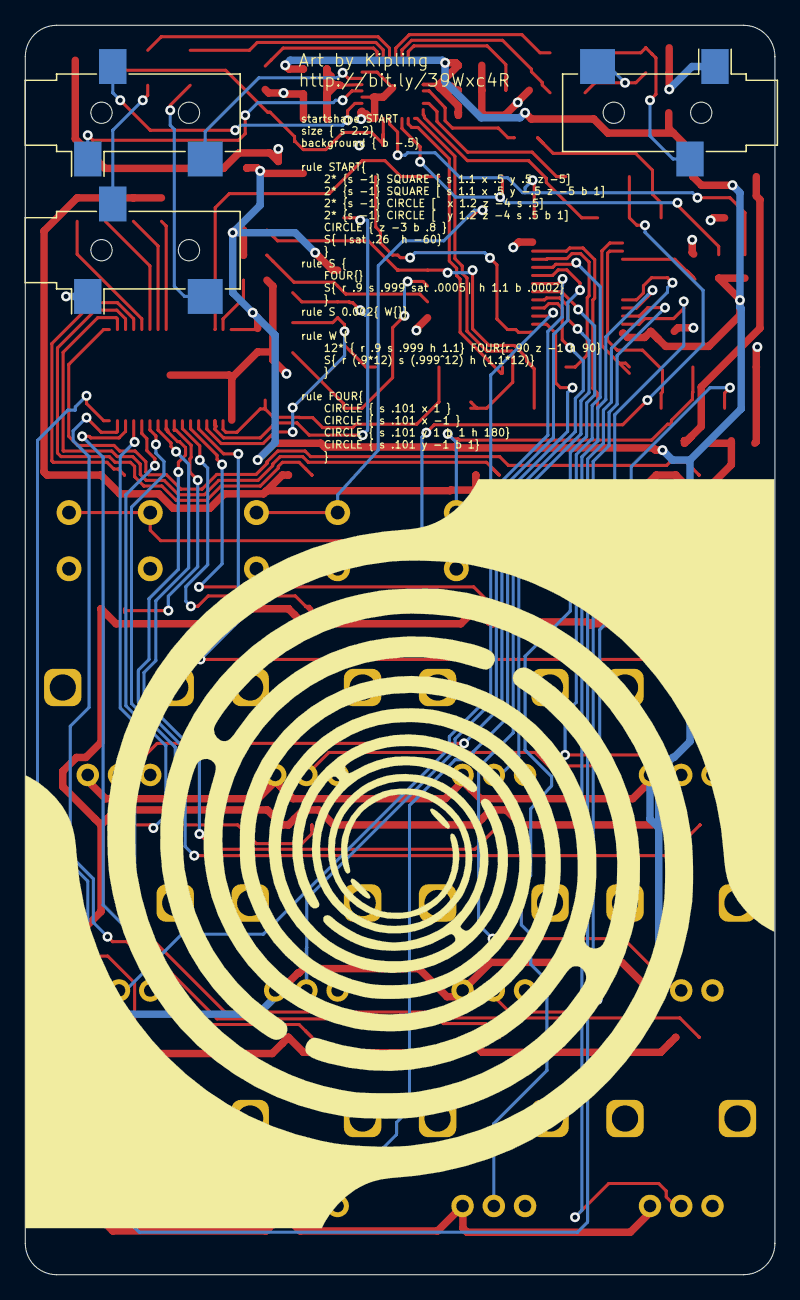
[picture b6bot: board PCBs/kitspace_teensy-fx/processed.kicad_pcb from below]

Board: 4 copper layers, 60.0 x 100.0 mm, 80 parts (3 on the bottom side), 77 nets.

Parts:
C1, C3, C6, C10, C11, C12, C17: 2.2uF; C_0805_2012Metric
C2, C4, C5, C7, C13: 0.1uF; C_0805_2012Metric
C8, C9, C14, C15: 1uF; C_1210_3225Metric
D1, D2, D3, D4, D5, D6, D7, D8, D9, D10, D11, D12, D13, D14, D15, D16, D17, D18, D19, D20: LED; LED_0805_2012Metric
J1, J2, J3: AudioJack3_Ground; Jack_3.5mm_CUI_SJ-3523-SMT_Horizontal
L1, L2: 600R; L_0805_2012Metric
R1, R2: 2.2K; R_0805_2012Metric
R3: 100R; R_0805_2012Metric
R4, R6, R7: 10k; R_0805_2012Metric
R5: 4.7k; R_0805_2012Metric
R8, R9: 100k; R_0805_2012Metric
RV1, RV2, RV3, RV4, RV5, RV6, RV7, RV8, RV9, RV10, RV11, RV12: R_POT; Potentiometer_Alps_RK09L_Single_Vertical
SW1, SW2, SW3, SW4: Switch_SW_Push; SW_PUSH_6mm
TP1, TP2, TP3, TP4, TP5, TP6, TP7, TP8: TestPoint; TestPoint_Pad_D1.0mm
U1: Teensy4.0; teensy4smt
U2: MCP1811A; SOT-23
U3: SGTL5000; QFN-32-1EP_5x5mm_P0.5mm_EP3.6x3.6mm
U4: 4067; SSOP-24_5.3x8.2mm_P0.65mm
U5: TLC5947DAP; HTSSOP-32-1EP_6.1x11mm_P0.65mm_EP5.2x11mm_Mask4.11x4.36mm
U6: W25Q128JVS; SOIC-8_5.23x5.23mm_P1.27mm

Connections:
+1V8: C17.1, TP7.1, U2.1, U3.30
+3V3: C1.1, C3.1, C4.1, C5.1, C10.1, C11.1, L1.1, R1.1, R2.1, R6.1, R7.1, RV1.1, RV2.1, RV3.1, RV4.1, RV5.1, RV6.1, RV7.1, RV8.1, RV9.1, RV10.1, RV11.1, RV12.1, TP6.1, U1.31, U2.2, U3.20, U4.24, U5.32, U6.8
+5V: L2.1, U1.33
+5VA: C12.1, D1.2, D2.2, D3.2, D4.2, D5.2, D6.2, D7.2, D8.2, D9.2, D10.2, D11.2, D12.2, D13.2, D14.2, D15.2, D16.2, D17.2, D18.2, D19.2, D20.2, L2.2
/SGTL audio/filter_audio_3v3: C6.1, C7.1, L1.2, U3.5
/mem_cs: R6.2, U1.8, U6.1
/pots buttons & LEDs/a0: RV1.2, U4.9
/pots buttons & LEDs/a1: RV4.2, U4.8
/pots buttons & LEDs/a2: RV7.2, U4.7
/pots buttons & LEDs/a3: RV10.2, U4.6
/pots buttons & LEDs/a4: RV2.2, U4.5
/pots buttons & LEDs/a5: RV5.2, U4.4
/pots buttons & LEDs/a6: RV8.2, U4.3
/pots buttons & LEDs/a7: RV11.2, U4.2
/pots buttons & LEDs/a8: RV3.2, U4.23
/pots buttons & LEDs/a9: RV6.2, U4.22
/pots buttons & LEDs/a10: RV9.2, U4.21
/pots buttons & LEDs/a11: RV12.2, U4.20
BCLK: U1.28, U3.24
GND: C1.2, C2.2, C3.2, C4.2, C5.2, C6.2, C7.2, C10.2, C11.2, C12.2, C13.2, C17.2, J1.S, J3.S, R4.2, R5.2, R8.2, R9.1, RV1.3, RV2.3, RV3.3, RV4.3, RV5.3, RV6.3, RV7.3, RV8.3, RV9.3, RV10.3, RV11.3, RV12.3, SW1.2, SW2.2, SW3.2, SW4.2, TP8.1, U1.1, U1.32, U2.3, U3.1, U3.3, U3.7, U3.31, U3.32, U3.33, U4.12, U5.1, U5.33, U6.4
I2S_IN: U1.10, U3.25
I2S_OUT: U1.9, U3.26
LRCLK: U1.27, U3.23
MCLK: R3.2, U1.30
MISO: TP5.1, U1.14, U6.2
MOSI: TP3.1, U1.13, U5.4, U6.5
unnamed: C2.1, U3.10
unnamed: C8.1, U3.14
unnamed: C8.2, J1.T, R8.1
unnamed: C9.1, U3.13
unnamed: C9.2, J1.R, R9.2
unnamed: C13.1, U3.15
unnamed: C14.1, U3.11
unnamed: C14.2, J3.T
unnamed: C15.1, U3.12
unnamed: C15.2, J3.R
unnamed: D1.1, U5.5
unnamed: D2.1, U5.6
unnamed: D3.1, U5.7
unnamed: D4.1, U5.8
unnamed: D5.1, U5.9
unnamed: D6.1, U5.10
unnamed: D7.1, U5.11
unnamed: D8.1, U5.12
unnamed: D9.1, U5.13
unnamed: D10.1, U5.14
unnamed: D11.1, U5.15
unnamed: D12.1, U5.16
unnamed: D13.1, U5.17
unnamed: D14.1, U5.18
unnamed: D15.1, U5.19
unnamed: D16.1, U5.20
unnamed: D17.1, U5.21
unnamed: D18.1, U5.22
unnamed: D19.1, U5.23
unnamed: D20.1, U5.24
unnamed: J2.R, U3.2
unnamed: J2.S, U3.4
unnamed: J2.T, U3.6
unnamed: R3.1, U3.21
unnamed: R4.1, U4.15
unnamed: R5.1, U5.31
unnamed: R7.2, U6.3, U6.7
SCL: R2.2, U1.26, U3.29
SCLK: TP1.1, U1.20, U5.3, U6.6
SDA: R1.2, U1.25, U3.27
led_latch: TP4.1, U1.23, U5.30
led_oe: TP2.1, U1.11, U5.2
pot_b0: U1.7, U4.10
pot_b1: U1.6, U4.11
pot_b2: U1.4, U4.14
pot_b3: U1.5, U4.13
pot_multiplex: U1.21, U4.1
sw_1: SW1.1, U1.2
sw_2: SW2.1, U1.3
sw_3: SW3.1, U1.24
sw_4: SW4.1, U1.29

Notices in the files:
PCBs/kitspace_spike_n_hold/processed.kicad_pcb:
spike and hold circuit (2X) CERN OHL V2 S 20200202 Chagas AM
PCBs/kitspace_ss_relay/processed.kicad_pcb:
v0.2 CC BY 4.0
PCBs/kitspace_temp_breakout/processed.kicad_pcb:
licensed under
CERN-OHL-W 2.0
